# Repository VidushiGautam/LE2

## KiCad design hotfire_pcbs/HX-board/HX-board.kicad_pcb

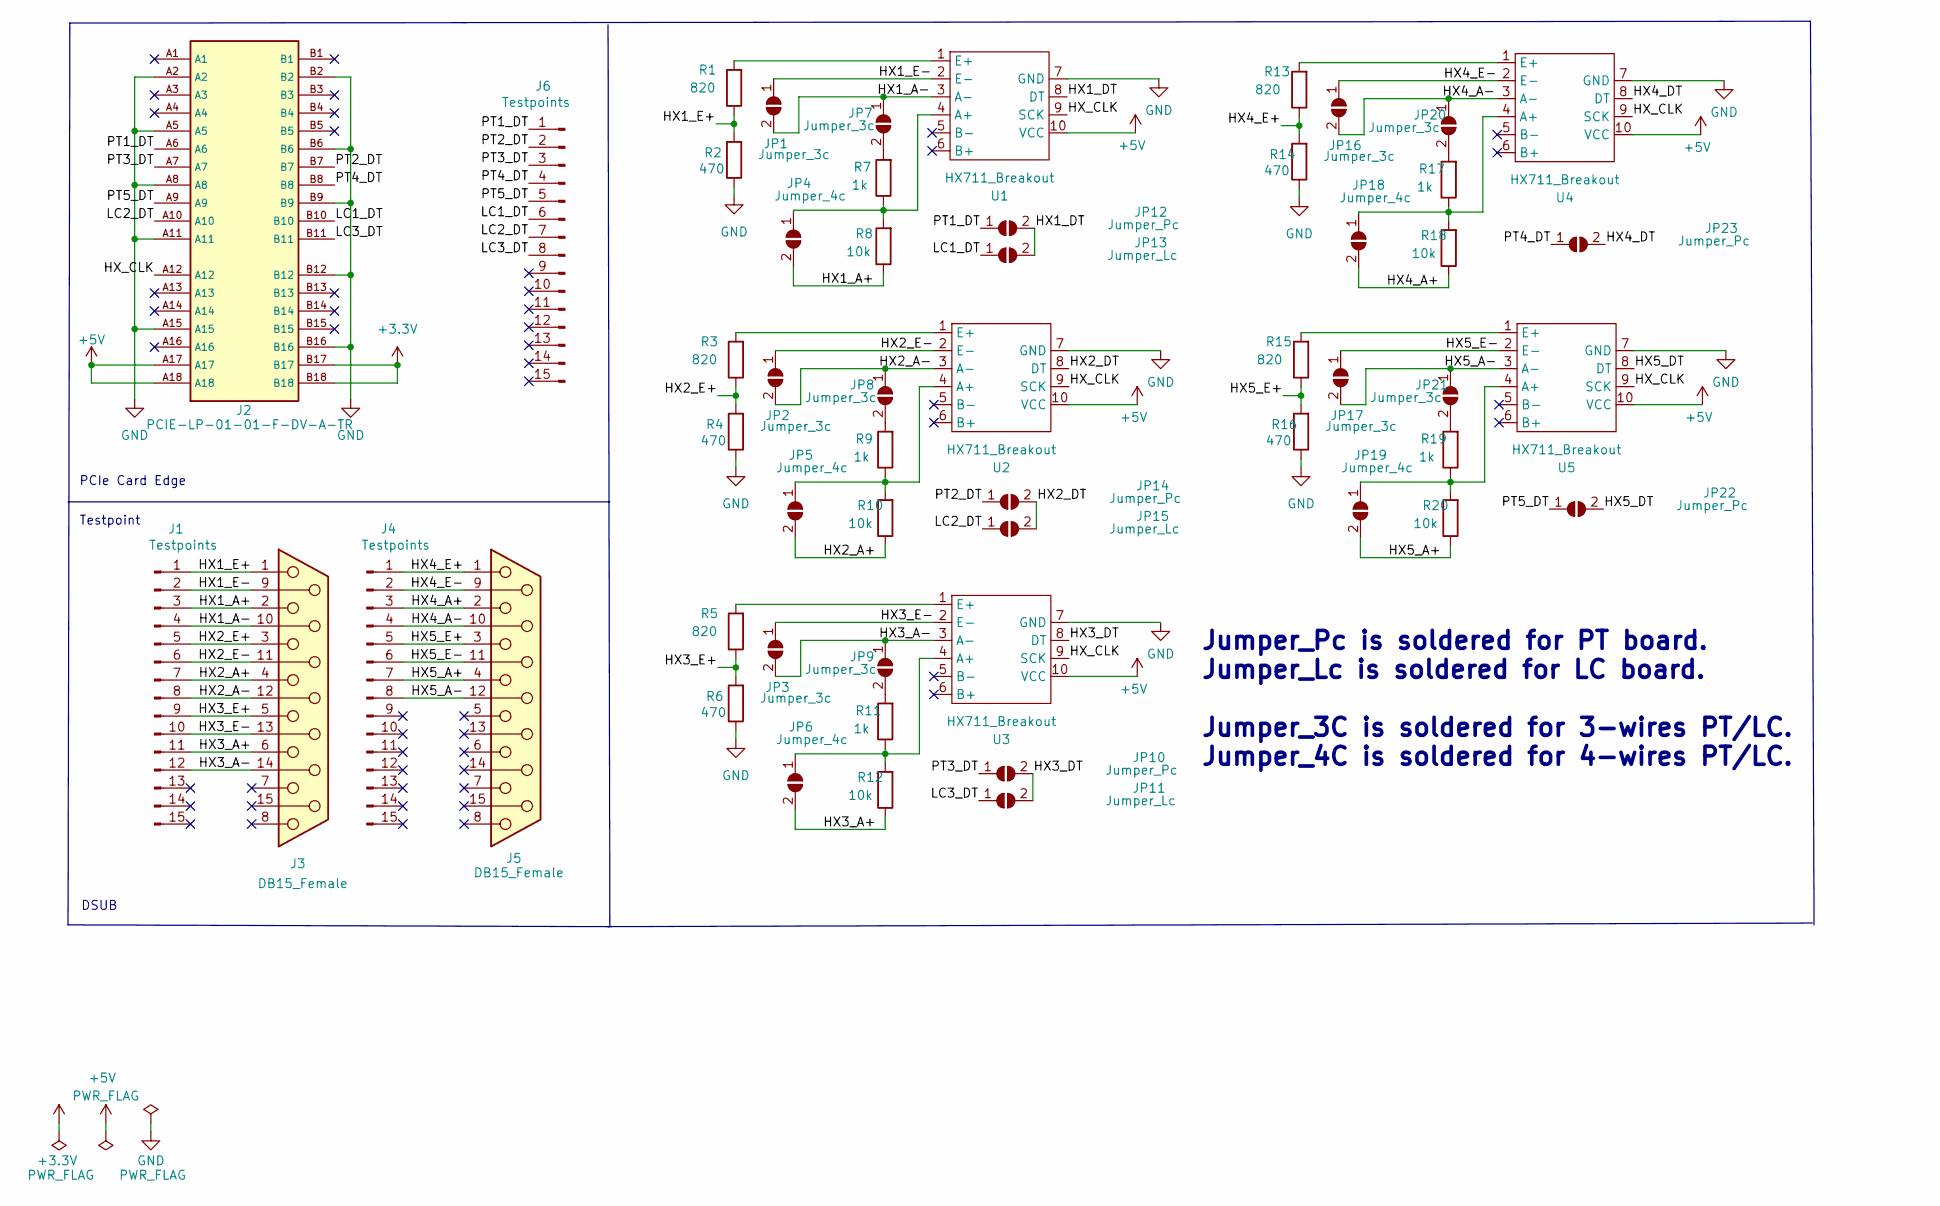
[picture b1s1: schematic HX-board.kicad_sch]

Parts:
J1, J4, J6: Testpoints; PinHeader_1x15_P2.54mm_Vertical
J2: PCIE-LP-01-01-F-DV-A-TR; PCIe_x1_card_edge; PARTREV B
J3, J5: DB15_Female; DSUB_622-015-260-042
JP1, JP2, JP3, JP7, JP8, JP9, JP16, JP17, JP20, JP21: Jumper_3c; SolderJumper-2_P1.3mm_Open_RoundedPad1.0x1.5mm
JP4, JP5, JP6, JP18, JP19: Jumper_4c; SolderJumper-2_P1.3mm_Open_RoundedPad1.0x1.5mm
JP10, JP12, JP14, JP22, JP23: Jumper_Pc; SolderJumper-2_P1.3mm_Open_RoundedPad1.0x1.5mm
JP11, JP13, JP15: Jumper_Lc; SolderJumper-2_P1.3mm_Open_RoundedPad1.0x1.5mm
R1, R3, R5, R13, R15: 820; R_0805_2012Metric
R2, R4, R6, R14, R16: 470; R_0805_2012Metric
R7, R9, R11, R17, R19: 1k; R_0805_2012Metric
R8, R10, R12, R18, R20: 10k; R_0805_2012Metric
U1, U2, U3, U4, U5: HX711_Breakout; HX711_Breakout_Board

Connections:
+3.3V: J2.B17, J2.B18
+5V: J2.A17, J2.A18, U1.10 (VCC), U2.10 (VCC), U3.10 (VCC), U4.10 (VCC), U5.10 (VCC)
/HX1_A+: J1.3, J3.2, JP4.2 (B), R8.1
/HX1_A-: J1.4, J3.10, JP1.2 (B), JP7.1 (A), U1.3 (A-)
/HX1_DT: JP12.2 (B), JP13.2 (B), U1.8 (DT)
/HX1_E+: J1.1, J3.1, R1.1, R2.2
/HX1_E-: J1.2, J3.9, JP1.1 (A), U1.2 (E-)
/HX2_A+: J1.7, J3.4, JP5.2 (B), R10.1
/HX2_A-: J1.8, J3.12, JP2.2 (B), JP8.1 (A), U2.3 (A-)
/HX2_DT: JP14.2 (B), JP15.2 (B), U2.8 (DT)
/HX2_E+: J1.5, J3.3, R3.1, R4.2
/HX2_E-: J1.6, J3.11 (P111), JP2.1 (A), U2.2 (E-)
/HX3_A+: J1.11, J3.6, JP6.2 (B), R12.1
/HX3_A-: J1.12, J3.14, JP3.2 (B), JP9.1 (A), U3.3 (A-)
/HX3_DT: JP10.2 (B), JP11.2 (B), U3.8 (DT)
/HX3_E+: J1.9, J3.5, R5.1, R6.2
/HX3_E-: J1.10, J3.13, JP3.1 (A), U3.2 (E-)
/HX4_A+: J4.3, J5.2, JP18.2 (B), R18.1
/HX4_A-: J4.4, J5.10, JP16.2 (B), JP20.1 (A), U4.3 (A-)
/HX4_DT: JP23.2 (B), U4.8 (DT)
/HX4_E+: J4.1, J5.1, R13.1, R14.2
/HX4_E-: J4.2, J5.9, JP16.1 (A), U4.2 (E-)
/HX5_A+: J4.7, J5.4, JP19.2 (B), R20.1
/HX5_A-: J4.8, J5.12, JP17.2 (B), JP21.1 (A), U5.3 (A-)
/HX5_DT: JP22.2 (B), U5.8 (DT)
/HX5_E+: J4.5, J5.3, R15.1, R16.2
/HX5_E-: J4.6, J5.11 (P111), JP17.1 (A), U5.2 (E-)
/HX_CLK: J2.A12, U1.9 (SCK), U2.9 (SCK), U3.9 (SCK), U4.9 (SCK), U5.9 (SCK)
/LC1_DT: J2.B10, J6.6, JP13.1 (A)
/LC2_DT: J2.A10, J6.7, JP15.1 (A)
/LC3_DT: J2.B11, J6.8, JP11.1 (A)
/PT1_DT: J2.A6, J6.1, JP12.1 (A)
/PT2_DT: J2.B7, J6.2, JP14.1 (A)
/PT3_DT: J2.A7, J6.3, JP10.1 (A)
/PT4_DT: J2.B8, J6.4, JP23.1 (A)
/PT5_DT: J2.A9, J6.5, JP22.1 (A)
GND: J2.A2, J2.A5, J2.A8, J2.A11, J2.A15, J2.B2, J2.B6, J2.B9, J2.B12, J2.B16, R2.1, R4.1, R6.1, R14.1, R16.1, U1.7 (GND), U2.7 (GND), U3.7 (GND), U4.7 (GND), U5.7 (GND)
unnamed: JP4.1 (A), R7.1, R8.2, U1.4 (A+)
unnamed: JP5.1 (A), R9.1, R10.2, U2.4 (A+)
unnamed: JP6.1 (A), R11.1, R12.2, U3.4 (A+)
unnamed: JP7.2 (B), R7.2
unnamed: JP8.2 (B), R9.2
unnamed: JP9.2 (B), R11.2
unnamed: JP18.1 (A), R17.1, R18.2, U4.4 (A+)
unnamed: JP19.1 (A), R19.1, R20.2, U5.4 (A+)
unnamed: JP20.2 (B), R17.2
unnamed: JP21.2 (B), R19.2
unnamed: R1.2, U1.1 (E+)
unnamed: R3.2, U2.1 (E+)
unnamed: R5.2, U3.1 (E+)
unnamed: R13.2, U4.1 (E+)
unnamed: R15.2, U5.1 (E+)

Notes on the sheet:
DSUB
Testpoint
Jumper_Pc is soldered for PT board. Jumper_Lc is soldered for LC board. Jumper_3C is soldered for 3-wires PT/LC. Jumper_4C is soldered for 4-wires PT/LC.
PCIe Card Edge

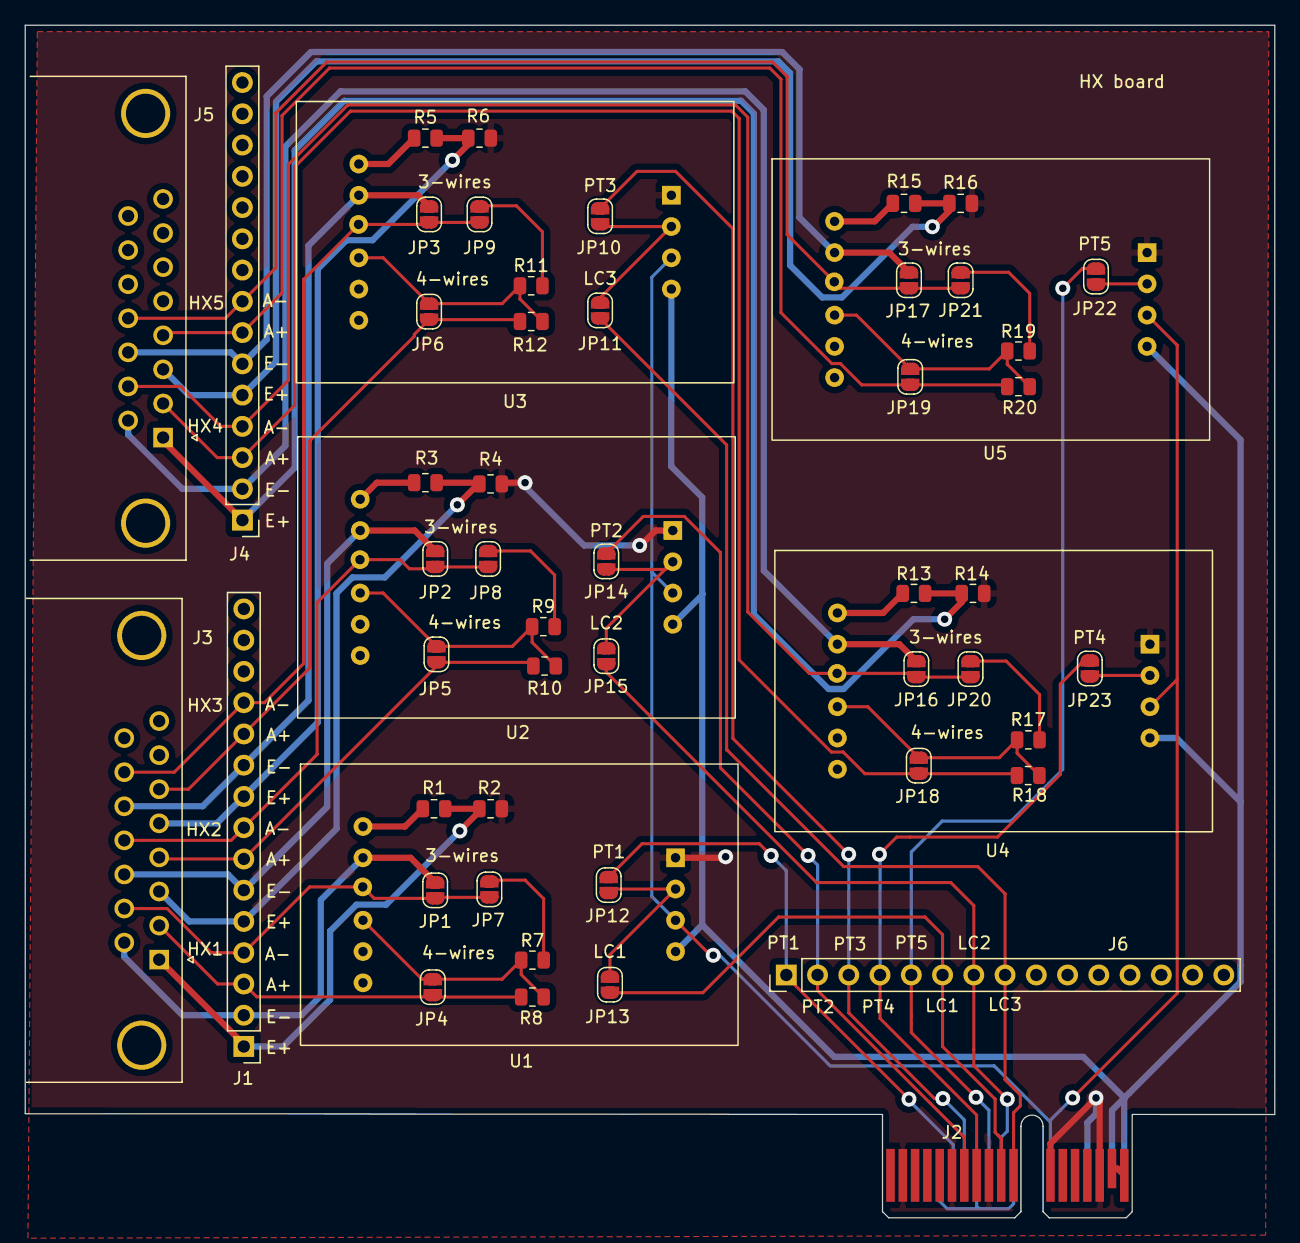
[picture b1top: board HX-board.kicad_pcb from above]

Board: 2 copper layers, 101.6 x 96.9 mm, 54 parts (0 on the bottom side), 52 nets.

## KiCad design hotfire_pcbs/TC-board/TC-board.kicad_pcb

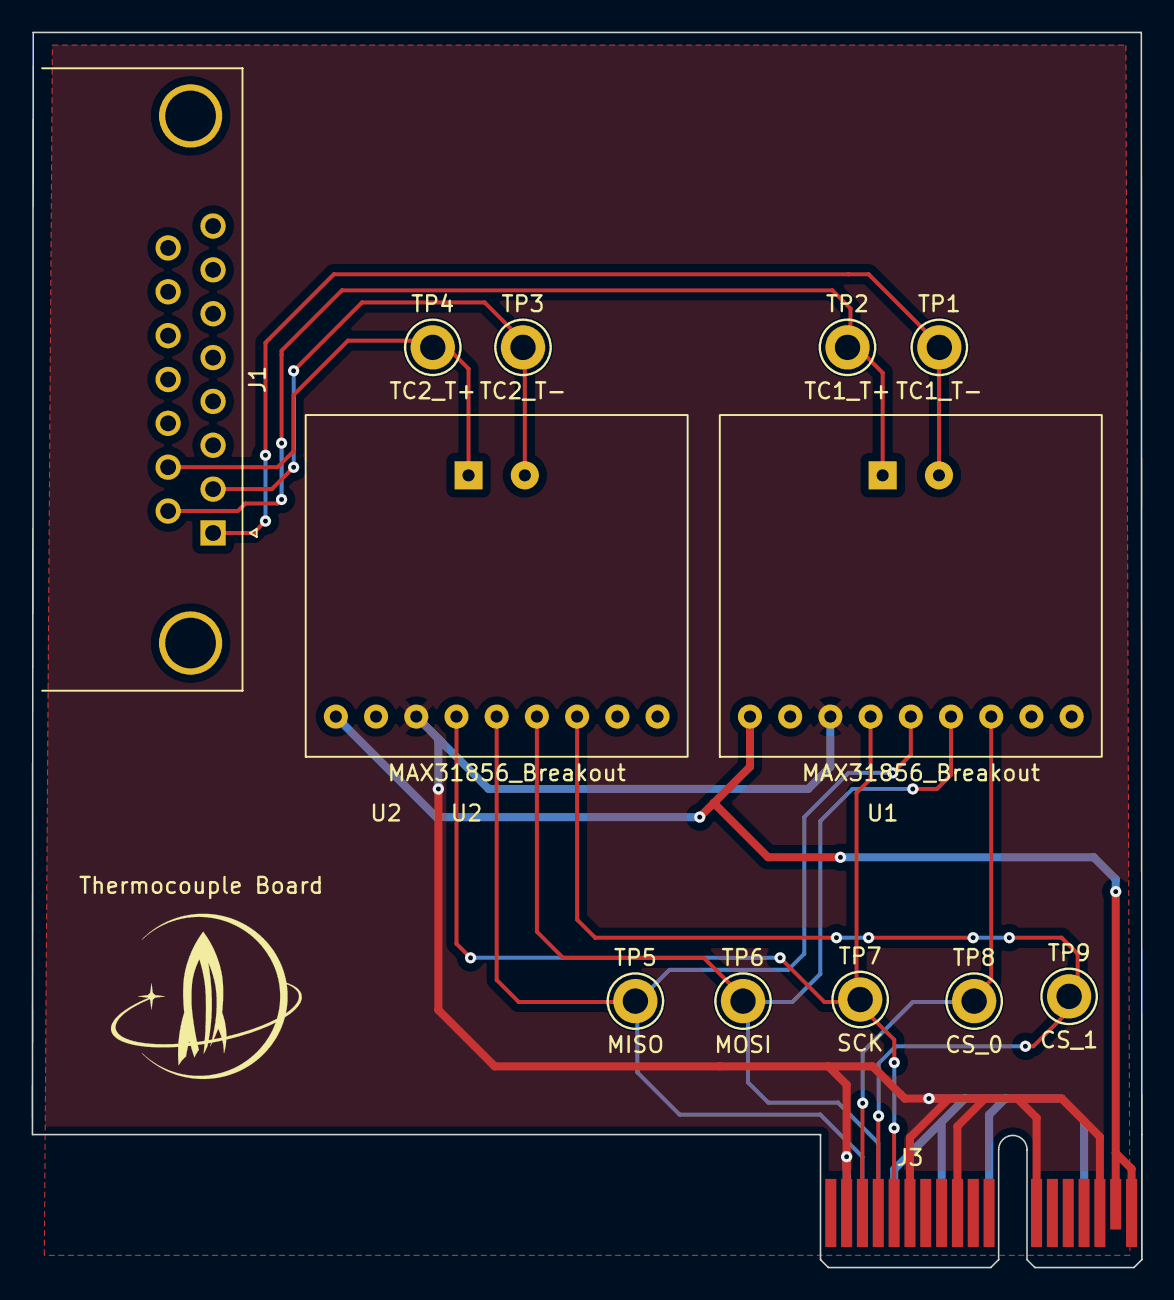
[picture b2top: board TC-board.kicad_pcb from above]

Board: 2 copper layers, 70.1 x 78.0 mm, 13 parts (0 on the bottom side), 11 nets.

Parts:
J1: DB15_Female; DSUB_622-015-260-042
J3: PCIE-LP-01-01-F-DV-A-TR; PCIe_x1_card_edge
TP1: TC1_T-; TestPoint_Keystone_5010-5014_Multipurpose
TP2: TC1_T+; TestPoint_Keystone_5010-5014_Multipurpose
TP3: TC2_T-; TestPoint_Keystone_5010-5014_Multipurpose
TP4: TC2_T+; TestPoint_Keystone_5010-5014_Multipurpose
TP5: MISO; TestPoint_Keystone_5010-5014_Multipurpose
TP6: MOSI; TestPoint_Keystone_5010-5014_Multipurpose
TP7: SCK; TestPoint_Keystone_5010-5014_Multipurpose
TP8: CS_0; TestPoint_Keystone_5010-5014_Multipurpose
TP9: CS_1; TestPoint_Keystone_5010-5014_Multipurpose
U1, U2: MAX31856_Breakout

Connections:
+3.3V: J3.B17, J3.B18, U1.11 (VIN), U2.11 (VIN)
/SPI_CS_0: J3.B3, TP8.1, U1.5 (CS)
/SPI_CS_1: J3.B4, TP9.1, U2.5 (CS)
/SPI_MISO: J3.A3, TP5.1, U1.7 (SDO), U2.7 (SDO)
/SPI_MOSI: J3.A4, TP6.1, U1.6 (SDI), U2.6 (SDI)
/SPI_SCK: J3.B5, TP7.1, U1.8 (SCK), U2.8 (SCK)
/TC1_T+: J1.9, TP2.1, U1.2 (T+)
/TC1_T-: J1.1, TP1.1, U1.1 (T-)
/TC2_T+: J1.10, TP4.1, U2.2 (T+)
/TC2_T-: J1.2, TP3.1, U2.1 (T-)
GND: J3.A2, J3.A5, J3.A8, J3.A11, J3.A15, J3.B2, J3.B6, J3.B9, J3.B12, J3.B16, U1.9 (GND), U2.9 (GND)

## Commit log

2023-03-17 TC Board Layout
2023-03-17 Changed JST to DSUB
2023-03-19 Revised schematics for HX711 board.
2023-03-19 Updated TC Board
2023-03-19 Updated TC Board Layout (as of March 19th)
2023-03-19 TC Board (Updated March 19th)
2023-03-23 Fixed card edge clearance violation
2023-03-23 Updated HX711 Board
2023-03-23 Updated HX711
2023-03-23 Changed solder jumper footprint to round pad.
2023-03-24 Revised components placement in layout.
2023-03-24 Finished wiring HX. Need review + silkscreen.
2023-03-24 Added silkscreen.
2023-08-23 Initial changes.
2023-08-25 Rearranged functions to have better flow.
2023-09-23 Fix a few compiling bugs. Still need to be tested
2023-09-26 Updated code to look nicer. Added a few structs.
2023-10-01 updated QD code, defined mosfet pins, added in the pressure venting and release states
2023-10-01 decided to only close press themselves and not do QD this time
2023-10-01 Updated DAQ/COM code.
2024-01-29 Commented out code from DAQ SENSE and DAQ POWER, also added if statement in DAQ Power for recieiving DAQ Sense data
2024-01-29 DAQPower_DAQSense
